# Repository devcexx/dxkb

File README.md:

# dxkb

## What is it?

dxkb is a keyboard firmware library purely developed in Rust, that provides the
functionality to build your own keyboard. It is mainly designed for my personal
use and for learning purposes. As of today, it only provides support for
building split keyboards on the STM32F411 microcontroller.

## What is it not?

dxkb is **not** a keyboard firmware that is provided ready to be flashed into a
MCU. The API that provides is designed considering that the final user will
define its own hardware configuration, main and ISR functions, as well as any
other functionality aside from the keyboard itself, that is not included on the
library (e.g. LEDs, OLED displays etc.)

## Design tenets

As a learning project, I prioritize the following principles during the development:
 - **Types first**: Most of the keyboard configuration happens through types, that
   defines the configuration of the firmware in compile time, without adding
   extra overhead, or possible errors in runtime. This library makes a heavy use
   of types for defining a lot of aspects of the device, such as the size of the
   key matrix, debouncing algorithms, etc. This also usually translate into a
   heavy use of macros, that help to define types and impls that are useful to
   achieve this purpose.
 
 - **No hardware abstraction frameworks**: As part of the learning process in
   embedded development, it is preferred to avoid the usage of frameworks that
   abstracts too much over the hardware, and working close to it instead.
   Usage of these kind of frameworks, like Embassy or RTIC is not contemplated
   as for now.
 
 - **Rust unstable**: Nightly versions of Rust are preferred to play with all the
   unstable Rust features. The main driver for using Rust unstable is the
   ability to use generic_const_exprs, that are just too cool to not use them,
   even though it is still an incomplete feature. A successful compilation is
   not guaranteed in any other Rust version than the specified by this
   repository.
 
 - **Some unsafe is fine**: For the sake of avoiding as much as possible using
   unwraps or useless error handling when some condition cannot be proven to the
   compiler in compile time, and add extra overhead to the final binary; using
   some unsafe code is fine from the perspective of this library. For example,
   there are places in this library where some UnsafeCell's are used instead of
   RefCells, to avoid the overhead of the RefCell's borrow checking in,
   especially considering the fact that the only supported MCU is single-core.
 
 - **Low number of external dependencies**: As a learning project, it is
   preferred to investigate and develop my own version of some components,
   instead of using already existing libraries that can fit the needs. Base
   libraries such as HAL, PACs and USB control libraries are used, but
   generally, building the functionality as part of the library is preferred.

## Features

 - Support for split keyboards (actually, it does not support anything else but
   split keyboards).
 
 - Key matrix:
   - Support for column to row and row to column scans.
   - Active-low press detection.
   - Support for key debouncing (Right now, only implemented an
     eager, per-key debouncing algorithm, see [QMK
     Docs](https://docs.qmk.fm/feature_debounce_type) for more information).
   - Support for input pins oversampling (Read multiple times the matrix input
     pins to ensure that the received signals are coming from presses and are
     not electrical noise).
   
 - Support for report keyboard HID protocol, that is NKRO by default. 
   Dual Boot + Report protocol support is still not implemented.
 
 - Debug endpoint that supports logging through a HID interface and debug
   command sending, such as commands to entering into the bootloader. Especially
   useful for PCBs that don't expose the STM32 debugging pins.
 
 - DMA-based serial communication across the two sides of the keyboard, up to 2
   MBaud with option for Full duplex and Half duplex, and automatic frame
   separation through the detection of IDLE signals in the line.
 
 - Split link: a low-footprint protocol built on top of serial that allows a
   reliable, bidirectional communication across the sides of the keyboard. This
   protocol combines capabilities from a link and transport protocols, having
   the ability to detect whether the link is up, negotiate the link
   establishment, and frame management, ensuring that the messages arrive to the
   other side in order, with no duplicates, and automatically retransmitting
   dropped frames if the peer couldn't confirm the reception of one.
 
 - Automatic USB master side detection and promotion.
 
 - Custom key definition: New keys can be built with ease on top of the default
   ones that can define their own logic when pressed or unpressed.

 - Multi layer, tree based layer definition: The keyboard supports the
   definition of multiple layers, that can be defined in a tree hierarchy
   defined through macros. In compile time, this layer hierarchy is flattened,
   so that there's no a performance penalty when leading with bigger layer
   trees.
 
 - Remote wakeup support: The keyboard may wake up their host when this latter
   one is suspended, after pressing a key.
 
 ## Examples
 
  - [Testing keyboard used for development purposes.](https://github.com/devcexx/dxkb/blob/master/crates/dxkb-main/src/targets/testkb_3x5/main.rs)
  - [My personal Lily58 keyboard firmware](https://github.com/devcexx/dxkb/tree/master/crates/dxkb-lily58l-stemcell), that uses [STeMCell](https://github.com/devcexx/STeMCell) as a drop-in replacement for the Arduino ProMicro, using a STM32F411 instead.

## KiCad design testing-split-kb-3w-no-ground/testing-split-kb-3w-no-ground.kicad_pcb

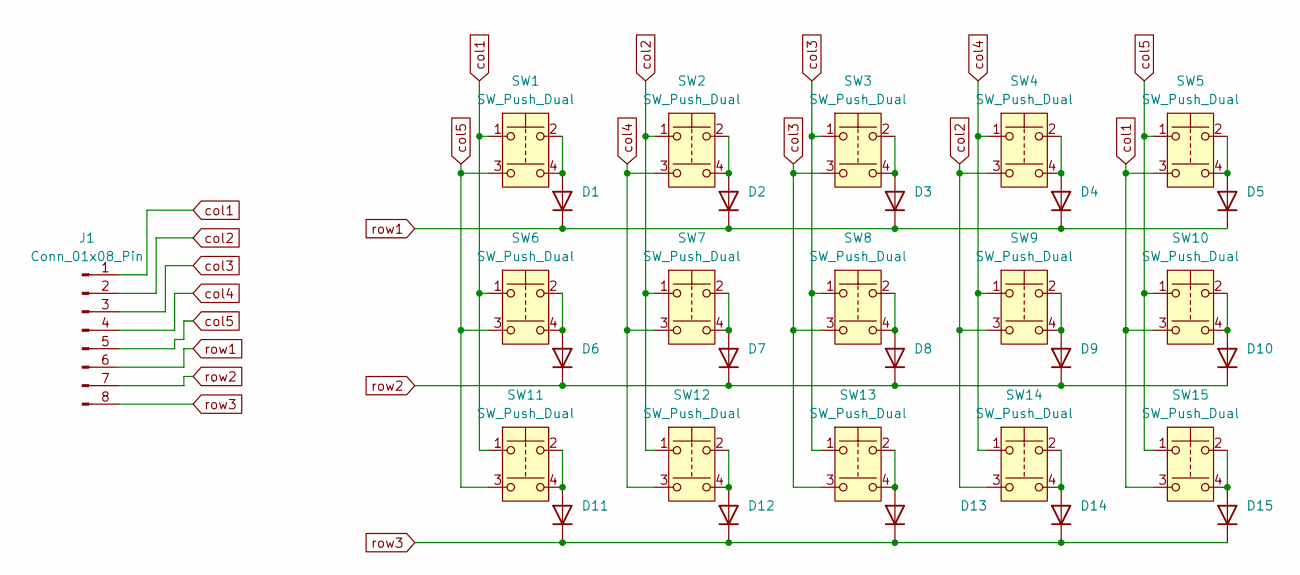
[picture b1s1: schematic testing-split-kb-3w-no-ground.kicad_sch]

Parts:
D1, D2, D3, D4, D5, D6, D7, D8, D9, D10, D11, D12, D13, D14, D15: 1N4148; D_DO-35_SOD27_P7.62mm_Horizontal_BothSides
J1: Conn_01x08_Pin; PinHeader_1x08_P2.54mm_Vertical
SW1, SW2, SW3, SW4, SW5, SW6, SW7, SW8, SW9, SW10, SW11, SW12, SW13, SW14, SW15: SW_Push_Dual; Kailh_socket_MX_reversible

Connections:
unnamed: D1.2 (A), SW1.2, SW1.4
unnamed: D2.2 (A), SW2.2, SW2.4
unnamed: D3.2 (A), SW3.2, SW3.4
unnamed: D4.2 (A), SW4.2, SW4.4
unnamed: D5.2 (A), SW5.2, SW5.4
unnamed: D6.2 (A), SW6.2, SW6.4
unnamed: D7.2 (A), SW7.2, SW7.4
unnamed: D8.2 (A), SW8.2, SW8.4
unnamed: D9.2 (A), SW9.2, SW9.4
unnamed: D10.2 (A), SW10.2, SW10.4
unnamed: D11.2 (A), SW11.2, SW11.4
unnamed: D12.2 (A), SW12.2, SW12.4
unnamed: D13.2 (A), SW13.2, SW13.4
unnamed: D14.2 (A), SW14.2, SW14.4
unnamed: D15.2 (A), SW15.2, SW15.4
col1: J1.1, SW1.1, SW5.3, SW6.1, SW10.3, SW11.1, SW15.3
col2: J1.2, SW2.1, SW4.3, SW7.1, SW9.3, SW12.1, SW14.3
col3: J1.3, SW3.1, SW3.3, SW8.1, SW8.3, SW13.1, SW13.3
col4: J1.4, SW2.3, SW4.1, SW7.3, SW9.1, SW12.3, SW14.1
col5: J1.5, SW1.3, SW5.1, SW6.3, SW10.1, SW11.3, SW15.1
row1: D1.1 (K), D2.1 (K), D3.1 (K), D4.1 (K), D5.1 (K), J1.6
row2: D6.1 (K), D7.1 (K), D8.1 (K), D9.1 (K), D10.1 (K), J1.7
row3: D11.1 (K), D12.1 (K), D13.1 (K), D14.1 (K), D15.1 (K), J1.8

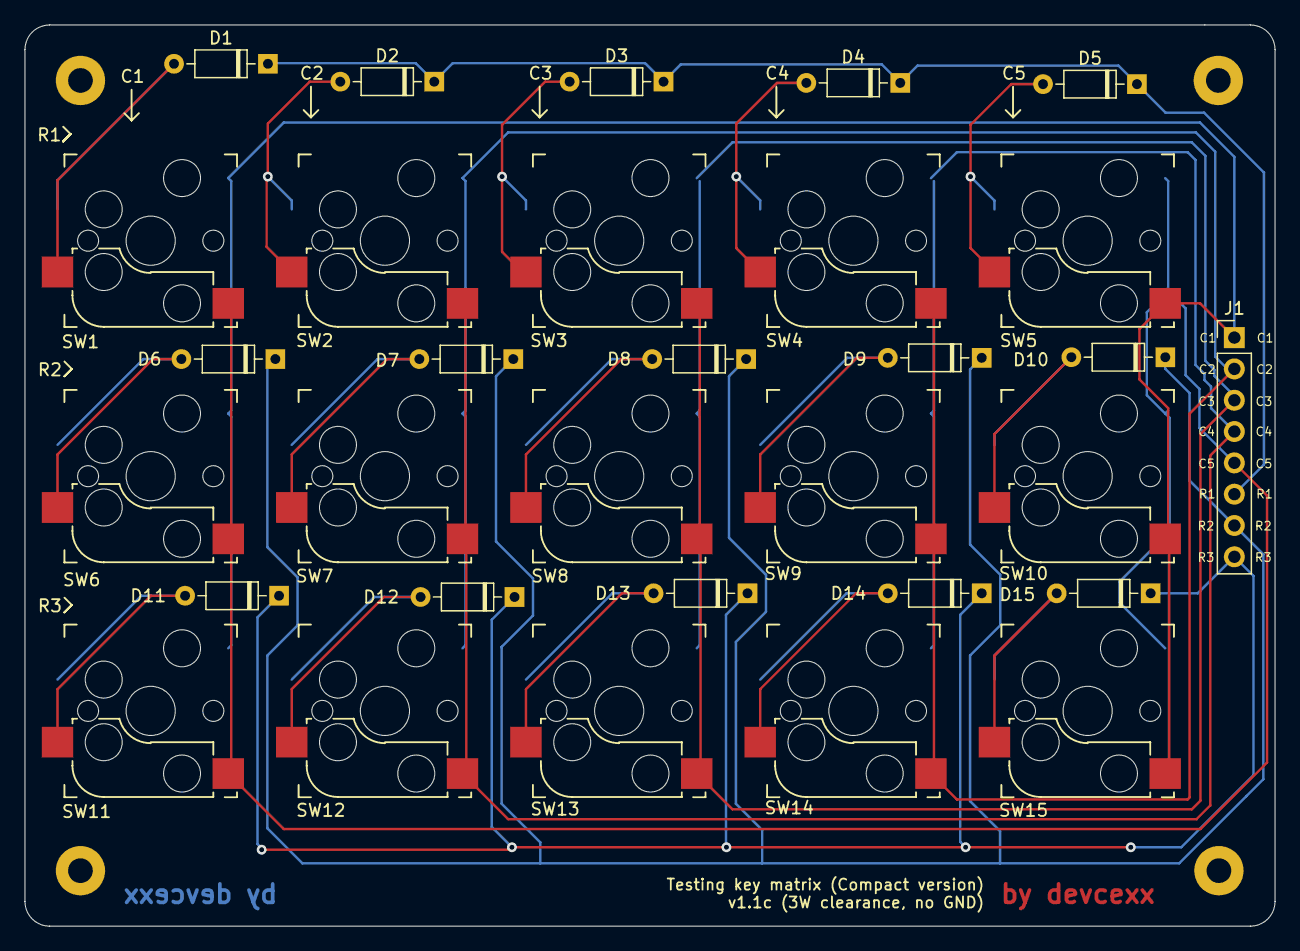
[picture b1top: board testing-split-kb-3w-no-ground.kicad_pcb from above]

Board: 2 copper layers, 101.4 x 73.1 mm, 31 parts (0 on the bottom side), 23 nets.

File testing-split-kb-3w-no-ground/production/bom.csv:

Designator,Footprint,Quantity,Value,LCSC Part #
"_4, _3, _2, ",,4,,
"D1, D10, D11, D12, D13, D14, D15, D2, D3, D4, D5, D6, D7, D8, D9",D_DO-35_SOD27_P7.62mm_Horizontal_BothSides,15,1N4148,
J1,PinHeader_1x08_P2.54mm_Vertical,1,Conn_01x08_Pin,
"SW1, SW10, SW11, SW12, SW13, SW14, SW15, SW2, SW3, SW4, SW5, SW6, SW7, SW8, SW9",Kailh_socket_MX_reversible,15,SW_Push_Dual,

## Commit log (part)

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2025-02-03 Initial commit
    Added test main, keyboard matrix peripheral, some GPIO abstractions
    extending the stm32f4xx_hal, and added some logging macros.
2025-02-04 WIP. Added HID key codes. Refactor debounce code
2025-02-04 Made key matrix to read input pins considering them active low
2025-02-05 Added support for row based matrix scan
2025-02-05 cargo fix cleaning
2025-02-05 Cargo fmt. Fixes in doc
2025-02-06 Added test code for triggering usb remote wake up
2025-02-06 Removed incorrect dep over stm32f4
    Its coexistence with stm32f4xx-hal may cause issues if the version
    doesn't exactly match the one used in stm32f4xx-hal. It is
    just better to access it through stm32f4xx_hal::pac
2025-02-06 Fixed keeping the test board led on when usb not suspended
2025-02-21 UART DMA + Split link WIP
2025-02-22 Resorted project in a workspace, and divided code in different crates
    This is basically intended for being able to build the
    dxkb-split-link-tester and being able to test the split link
    directly from the computer instead of depending on the STM32 for
    that. This package will depend on dxkb-split-link and dxkb-common
    that now have became architecture agnostic.
2025-02-22 Link sync working with the link tester
    - Reworked CRC calculation which was wrong af.
    - Made manual read of the serial port in the split link tester
    for better detecting idle conditions.
    - Discard of the garbage in the RX serial system buffers
    before running the tester.
2025-03-08 Keep going with the split link implementation.
    - Now the link itself and its tester (somehow) works when running in the PC.
    I've successfully able to transmit a small MP3 file through it.
    - The tester is still limited to low speeds because using a USB to serial
    converter makes hard to determine when a packet has finished transmitting.
    - Still needs to be tested on a real STM32 environment.
    - There's still missing features:
2025-03-08 Cleaned up old src folder
2025-03-08 Removed incorrect package declaration in workspace toml
2025-03-10 Fixed a bug in the DMA UART reader that makes the frame length to be incorrectly identified when reaching the end of the ring buffer. Implemented DMA UART transfer function
2025-03-10 Rebuild Clock API to make sure clock wrappings are properly handled
2025-03-10 Fixed DWT Clock not working when debug probe is not connected
2025-03-15 Moved DWT clock impl to peripherals. Drafted TIM-based clock impl
2025-03-15 Cargo fix
2025-03-16 Moved bit matrix generic implementation out of key matrix
2025-03-27 WIP keyboard core functionality
2025-03-28 Updated split link interface for limited polling. First keyboard impl. Implemented testing 4x4 single sided keyboard
    (Untested)
2025-04-21 Added OpenOCD debugging config
2025-04-21 Added testing split key matrix pcb
2025-05-04 Added multiple new versions of the testing pcb for testing crosstalk with different layouts
2025-05-04 Added OpenOCD left and right configurations
2025-05-04 Added testing kb 3x5 entry point
2025-05-04 Added side feature for dxkb-main and testkb_3x5 target
2025-05-15 Added USB master sensing trait
2025-05-15 Fail transfers through split link when link is down
2025-06-07 Updated compiler version
2025-06-07 Supported forced usb mode for the testing 3x5 kb
2025-06-22 Implemented initial version of the layers! proc macro.
    This proc-macro allows to define multlayouts with ease,
    and includes the following features:
    - Full integration with usbd-hid enum: each defined key
    corresponds to an entry in the usbd-hid KeyboardUsage enum,
    meaning that any standard HID can be mapped with this macro.
    The macro features also a set of aliases to simplify the
2025-08-10 Initial implementation of custom keys.
    This feature allows to customize the type of a logical key in the
    keyboard, allowing the user to perform any arbitrary action when
    a key changes the state in the matrix. This is done by implementing
    the HandleKey trait over a user defined type, that will determine
    which action will be ran with each key.
    It is also responsability of the HandleKey to add or remove
2025-08-10 Cargo check && cargo fmt
2025-08-10 Added layers! proc macro support for arbitrary aliases via macro_rules.
    With the new implementation of custom key type definition,
    the layers! proc macro becomes less useful if it doesn't
    support custom key definitions as well.
    This commits makes more flexible the definition of aliases
    for keys by removing the hardcoded keymap.rs from the
    dxkb-proc-macro, and delegating the mappings between the aliases
2025-08-24 Added alias_resolver field to the layers proc macro
    This field allows users to specify a macro_rules path that will
    be used for resolving aliases of the keys. If no specified,
    then the default (dxkb_core::default_key_from_alias), will be used
    and therefore it will use the default key type. Check the definition
    of this macro for seeing an example of an implementation of this
    kind of macros.
2025-12-23 Fixed build error
2026-01-12 WIP HID interface
2026-01-16 Implemented Report HID protocol and Consumer Control HUT.
2026-01-16 Cargo fmt && cargo fix
2026-01-16 Added Device ID to LinkProbe and Sync frames in Split link.
    I have the issue that, when testing on my testing board with two STM32,
    and one of them is turned off, but both of them are connected through serial,
    the serial works as if TX and RX are connected between them. Because of that
    it is possible that the split link can perform a connection between itself.
    For preventing overcomplicating the handshake process, I'm just adding a device
    ID to the LinkProbe and the Sync frames, so that if a device receives a
2026-01-16 Fixed invalid HID report
2026-01-16 Minor changes to HID and keys APIs. Update examples with a Custom Key
2026-02-21 Implementation of half-duplex USART
2026-02-22 Added custom Ringbuffer implementation
    It is not the first time that I feel that the ringbuffer library
    is kinda missing some stuff, like efficient ways to write
    multiple values inside the rb (mainly considering arrays of bytes),
    being able to read them, quickly dropping N elements, and
    operations in both the head and the tail of the buffer. I just
    ended up building quickly my own implementation. Obviously, it is
2026-02-22 Added HID debug IN endpoint
    I will install and test dxkb in some STeMCell in where I don't have
    access to the ITM. Therefore, just creating a (scrappy) HID IN
    endpoint for getting access to the logs the MCU generates. This
    implementation should be temporary because since now the UsbDev
    is owned by the ReportHidKeyboard struct, now the Keyboard has
    context about the debugging endpoint, which probably should not.
2026-02-24 Initial working version the DXKB Lily58L running on a STeMCell
    Includes various fixes here and there, including:
    - Fixes layer stack logic.
    - Added more common keys aliases.
    - Added a feature for entering in DFU mode by sending some HID data to the debug endpoint.
    - Added InputPins implementations for normal pins, without needing them to be in the same port.
    - Removed some unwanted logging messages. Downgraded some debug messages to trace.
2026-03-02 Extracted debug feature as an independent feature from the HID keyboard
    Now the new trait UsbFeature allows to define things that an USB
    might do, taking ownership of one or more endpoints. With this,
    each part of the code can define its own features (e. g, the
    "debug" feature, or the "keyboard" feature), and the final user
    keyboard implementation will take the ownership of initializing
    them and polling them.
2026-03-02 Added key matrix input pins oversampling.
    Right now, they keyboard matrix hardcodes a 10 cycle delay between
    enabling the output pin and reading the value from the input pins,
    because 1) We need to wait until GPIO stabilizes its value after
    changing it and 2) I've seen noise and cross-talk between the
    input pins when a output pins change, that we had to wait to
    dissipate before making a good reading.
2026-03-04 Added support for remote wakeup.
    Now, if the keyboard detects that usb remote wakeup is enabled,
    it will try to send a wakeup signal to the host once a key
    has been added to the list of pressed keys in the keyboard usb
    feature.
2026-03-04 Updated Rust compiler to latest nightly
2026-03-05 Reduced times for the default split link timings
2026-03-05 Added README
2026-03-10 Added layer change synchronization logic.
    Before this commit, there was no attempt from the keyboard to ensure
    that, when switching between layers, to properly notify the keys
    that they have been pressed or released, preventing those calls to
    go in pairs (ensure in release event is emitted for each pressed event).
    That lead to strange behaviours like:
    - User presses key 'A'. The computer receives the 'A' keystroke.
2026-04-03 Fixed possible column ghosting due to unhandled matrix diodes capacitance
    This commit prevents the capacitance of the matrix diodes to make the input lines
    of the matrix to take more than expected to reach high from low (~15 us), due to
    the capacitance generated by the diodes in the matrix and the high impedance of the line,
    coming from the pull-up resistors of the input lines. This is fixed by, on every scan
    temporarily makes the input lines to become outputs, and writing an one to 1, and instantly
    going making them back inputs again. This allows the capacitance of the input lines to
2026-04-05 Implemented logical masked key state. Set OSPEEDR to low.
    This change updates the number of internal states that each
    key has inside the keyboard state. Originally, there was no
    difference between the physical state (released, pressed), and
    the internal key state. However, this, combined with the
    layer sync process (when switching layers, release the old keys
    and press the new ones) was making too easy to have unintended
2026-04-05 Added column capacitance notes
2026-06-24 Bumped to latest nightly compiler
